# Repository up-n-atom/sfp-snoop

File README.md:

# sfp-snoop

SFP(+) cape for the [VCC-GND](https://vcc-gnd.com) [YD-RP2040](http://152.32.187.208:8080/yd-data/YD-RP2040/) pending a few modifications.

## Necessary YD-RP2040 Modifications

1. __Remove__ *D2, F1, U1, C1, C2*
2. __Bridge__ *D2* pins 1 and 2 with a 0Ohm 0603 resistor

__U1__ *(ME6215C33M5G)* and supporting components on the YD-RP2040 are replaced by __U1__ *(AIC1221-33GY3TR)* on the sfp-snoop 

## Pinout

| YD-RP2040 | [SFP (INF-8074i)](https://members.snia.org/document/dl/26184) | Transceivers |
| --        | --              | -- |
| 7 (GP5 - *USART1 RX*)   | 2 | Huawei SmartAX MA5671A, Alcatel-Lucent G-010S-P, BFW WAS-110 UART TX |
| 12 (GP8 - *USART1 TX*)  | 3 | Nokia G-010S-A UART RX |
| 9 (GP6 - *I2C1 SDA*)    | 4 | |
| 10 (GP7 - *I2C1 SCL*)   | 5 | |
| 11 (GP9 - *USART1 RX*)  | 6 | Nokia G-010S-A UART TX |
| 6 (GP4 - *USART1 TX*)   | 7 | Huawei SmartAX MA5671A, Alcatel-Lucent G-010S-P, BFW WAS-110 UART RX |
| 5 (GP3)                 | 8 | |
| 29 (GP22)               | 9 | |

* Short JP1
* Short R10 jumper to pin 37 (GP23) for user button power switch, or populate R10 with a 10KOhm 0603 resistor to access RGB LED (GP23)

## Bill of Materials

Total cost for single unit, incl. YD-RP2040 is around $5 USD.

| Ref.            | Value  | [LCSC](https://www.lcsc.com/) | Qty. |
| --              | --     | --                            | --:  |
| C1, C2          | 4.7uF  | [C1872](https://www.lcsc.com/product-detail/Multilayer-Ceramic-Capacitors-MLCC-SMD-SMT_Samsung-Electro-Mechanics-CL31B475KAHNNNE_C1872.html) | 2    |
| C3, C6, C9, C11 | 0.1uF  | [C282519](https://www.lcsc.com/product-detail/Multilayer-Ceramic-Capacitors-MLCC-SMD-SMT_CCTC-TCC0603X7R104K500CT_C282519.html) | 4    |
| C4              | 150uF   | [C542620](https://www.lcsc.com/product-detail/Tantalum-Capacitors_PANASONIC-6TPE150MAPB_C542620.html) | 1    |
| C7, C10         | 1uF    | [C59302](https://www.lcsc.com/product-detail/Multilayer-Ceramic-Capacitors-MLCC-SMD-SMT_FH-Guangdong-Fenghua-Advanced-Tech-0603B105K250NT_C59302.html) | 2    |
| C5, C8         | 0.01uF | [C525264](https://www.lcsc.com/product-detail/Multilayer-Ceramic-Capacitors-MLCC-SMD-SMT_PSA-Prosperity-Dielectrics-FN18X103K500PSG_C525264.html) | 2    |
| F1              | 2A     | [C261954](https://www.lcsc.com/product-detail/Resettable-Fuses_TLC-Electronic-TLC-NSMD100_C261954.html) | 1    |
| J1              | SFP+   | [C210158](https://www.lcsc.com/product-detail/Card-Edge-Connectors_TE-Connectivity-1367073-1_C210158.html) | 1    |
| J1 (Optional)   | SFP+ Cage   | [C7429382](https://www.lcsc.com/product-detail/Connector-Shells_HCTL-HC-SFP-03L_C7429382.html) | 1    |
| R1-R10           | 10KOhm | [C25804](https://www.lcsc.com/product-detail/Chip-Resistor-Surface-Mount_UNI-ROYAL-Uniroyal-Elec-0603WAF1002T5E_C25804.html) | 9 |
| U1              | AIC1221-33GY3TR | [C211622](https://www.lcsc.com/product-detail/Linear-Voltage-Regulators-LDO_AIC-Analog-Integrations-AIC1221-33GY3TR_C211622.html) | 1 |
| U2              | AP2191WG-7 | [C141321](https://www.lcsc.com/product-detail/Power-Distribution-Switches_Diodes-Incorporated-AP2191WG-7_C141321.html) | 1 |

| Ref.             | Value  | [AliExpress](https://www.aliexpress.com/) | Qty. |
| --               | --     | --                                        | --:  |
| J2, J3 *sfp-snoop* | Female | [2.54mm pitch, 20-pin Female Header](https://www.aliexpress.com/item/4000386969080.html) | 1 |

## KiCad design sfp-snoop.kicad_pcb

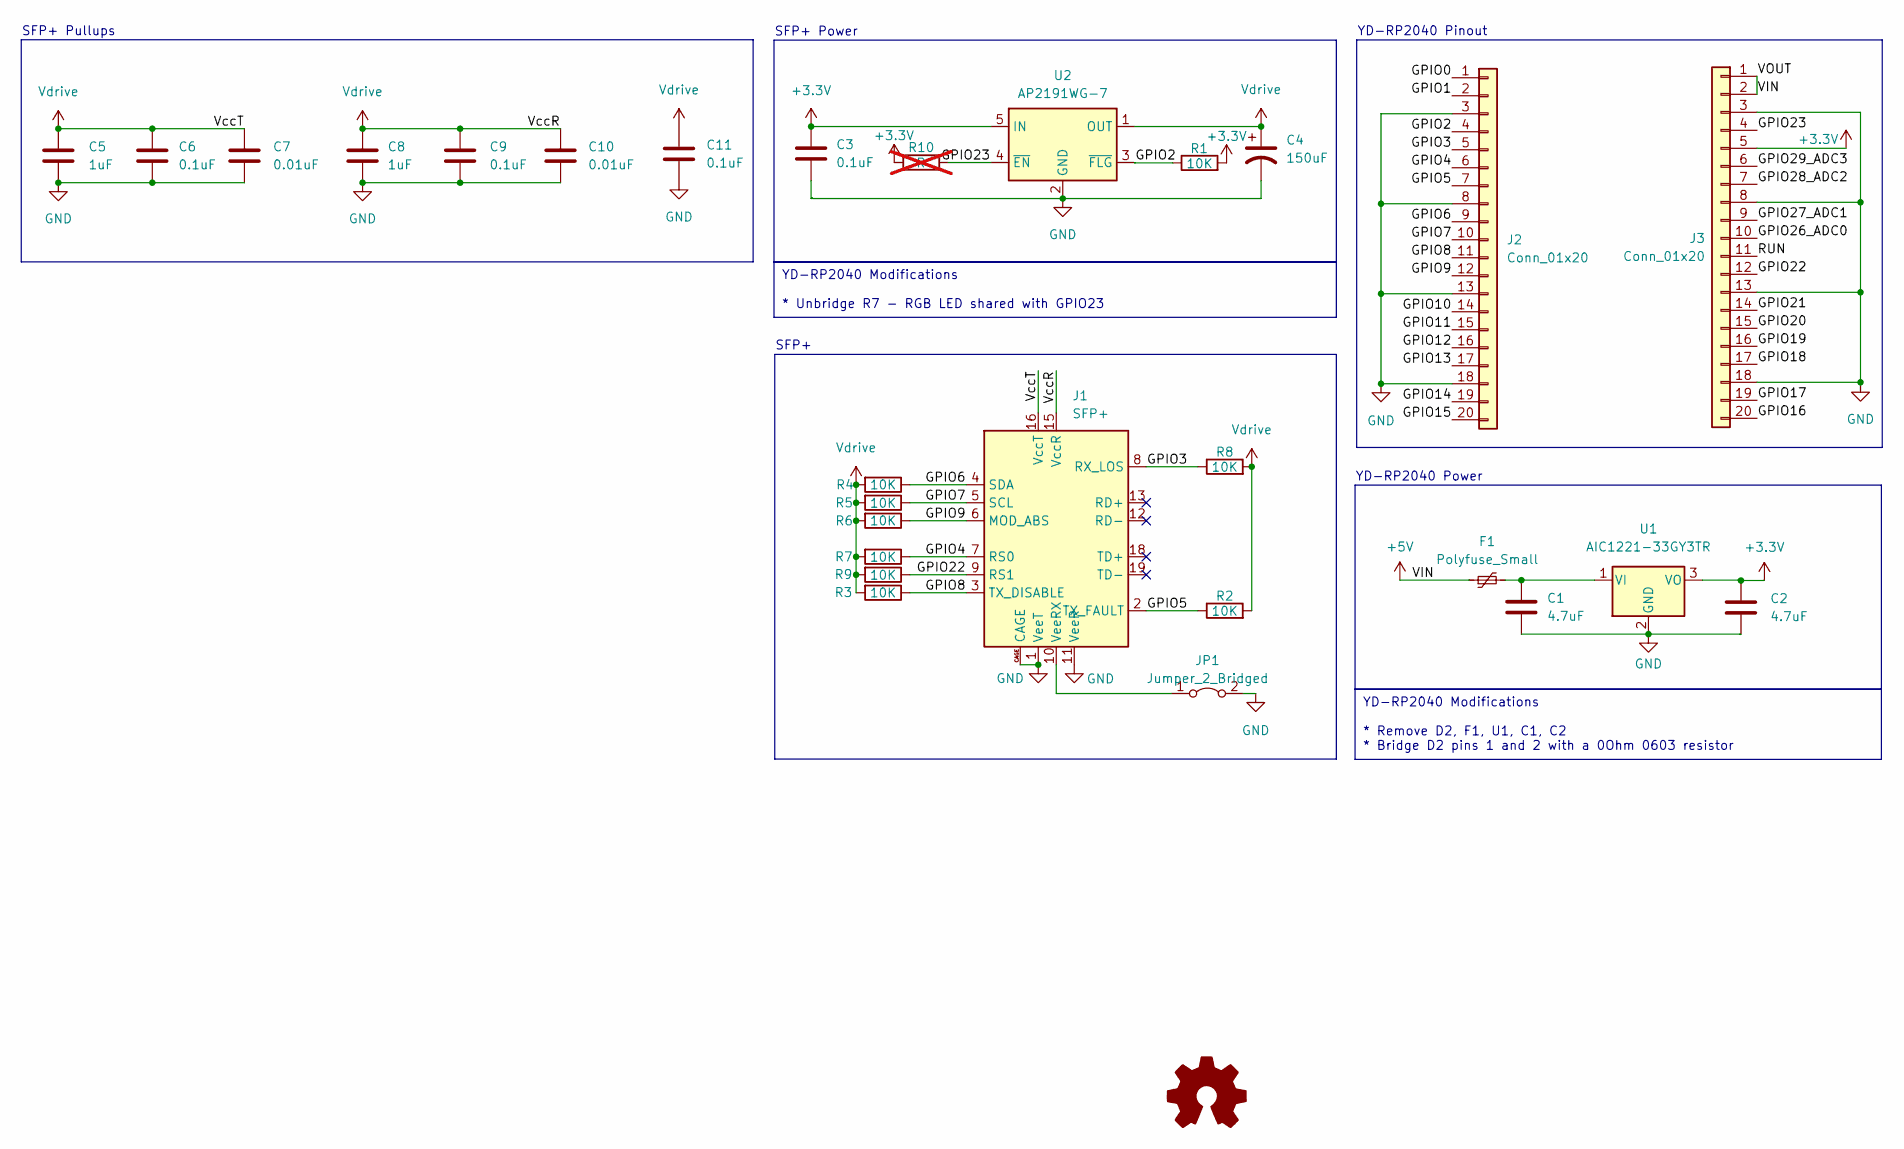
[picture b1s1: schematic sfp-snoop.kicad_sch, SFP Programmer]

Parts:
C1, C2: 4.7uF; C_1206_3216Metric; LCSC C1872
C3, C6, C9, C11: 0.1uF; C_0603_1608Metric; LCSC C282519
C4: 150uF; CP_EIA-3528-21_Kemet-B; LCSC C542620
C5, C8: 1uF; C_0603_1608Metric; LCSC C59302
C7, C10: 0.01uF; C_0603_1608Metric; LCSC C525264
F1: Polyfuse_Small; C_1206_3216Metric
J1: SFP+; Connector_SFP_and_Cage; LCSC C210158
J2, J3: Conn_01x20; PinSocket_1x20_P2.54mm_Vertical
JP1: Jumper_2_Bridged; SolderJumper-2_P1.3mm_Open_TrianglePad1.0x1.5mm
R1, R2, R3, R4, R5, R6, R7, R8, R9: 10K; R_0603_1608Metric; LCSC C25804
R10: R; R_0603_1608Metric; not fitted
U1: AIC1221-33GY3TR; SOT-223-3_TabPin2; LCSC C211622
U2: AP2191WG-7; SOT-23-5; LCSC C141321

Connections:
+3.3V: C2.1, C3.1, J3.5, R1.2, R10.1, U1.3 (VO), U2.5 (IN)
+5V: F1.1, J3.1, J3.2
/GPIO0: J2.1
/GPIO1: J2.2
/GPIO2: J2.4, R1.1, U2.3 (~FLG)
/GPIO3: J1.8 (RX_LOS), J2.5, R8.1
/GPIO4: J1.7 (RS0), J2.6, R7.1
/GPIO5: J1.2 (TX_FAULT), J2.7, R2.1
/GPIO6: J1.4 (SDA), J2.9, R4.1
/GPIO7: J1.5 (SCL), J2.10, R5.1
/GPIO8: J1.3 (TX_DISABLE), J2.11, R3.1
/GPIO9: J1.6 (MOD_ABS), J2.12, R6.1
/GPIO10: J2.14
/GPIO11: J2.15
/GPIO12: J2.16
/GPIO13: J2.17
/GPIO14: J2.19
/GPIO15: J2.20
/GPIO16: J3.20
/GPIO17: J3.19
/GPIO18: J3.17
/GPIO19: J3.16
/GPIO20: J3.15
/GPIO21: J3.14
/GPIO22: J1.9 (RS1), J3.12, R9.1
/GPIO23: J3.4, R10.2, U2.4 (~EN)
/GPIO26_ADC0: J3.10
/GPIO27_ADC1: J3.9
/GPIO28_ADC2: J3.7
/GPIO29_ADC3: J3.6
/RUN: J3.11
GND: C1.2, C2.2, C3.2, C4.2, C5.2, C6.2, C7.2, C8.2, C9.2, C10.2, C11.2, J1.1 (VeeT), J1.11 (VeeR), J1.14 (VeeR), J1.17 (VeeT), J1.20 (VeeT), J1.CAGE, J2.3, J2.8, J2.13, J2.18, J3.3, J3.8, J3.13, J3.18, JP1.2 (B), U1.2 (GND), U2.2 (GND)
unnamed: J1.10 (VeeRX), JP1.1 (A)
unnamed: C1.1, F1.2, U1.1 (VI)
Vdrive: C4.1, C5.1, C6.1, C7.1, C8.1, C9.1, C10.1, C11.1, J1.15 (VccR), J1.16 (VccT), R2.2, R3.2, R4.2, R5.2, R6.2, R7.2, R8.2, R9.2, U2.1 (OUT)

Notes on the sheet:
YD-RP2040 Modifications * Unbridge R7 - RGB LED shared with GPIO23
YD-RP2040 Modifications * Remove D2, F1, U1, C1, C2 * Bridge D2 pins 1 and 2 with a 0Ohm 0603 resistor
SFP+
SFP+ Pullups
SFP+ Power
YD-RP2040 Pinout
YD-RP2040 Power

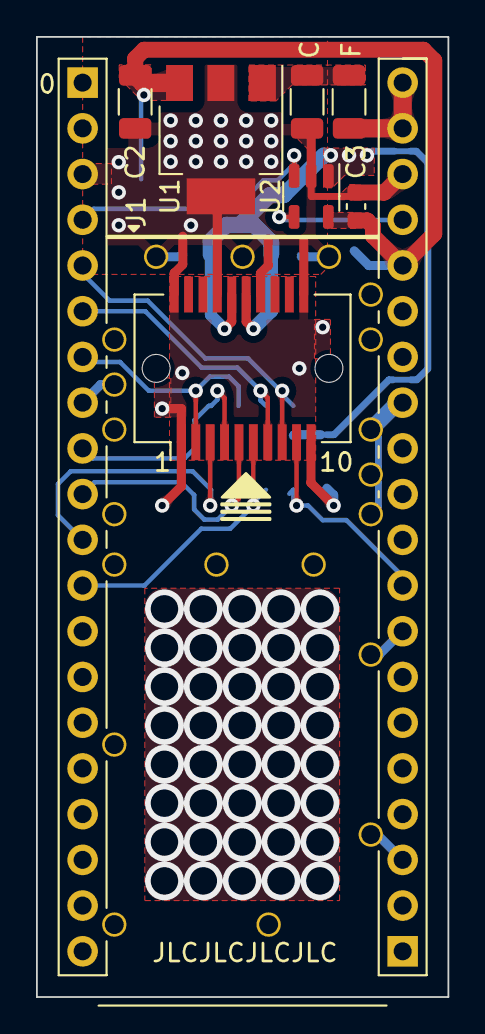
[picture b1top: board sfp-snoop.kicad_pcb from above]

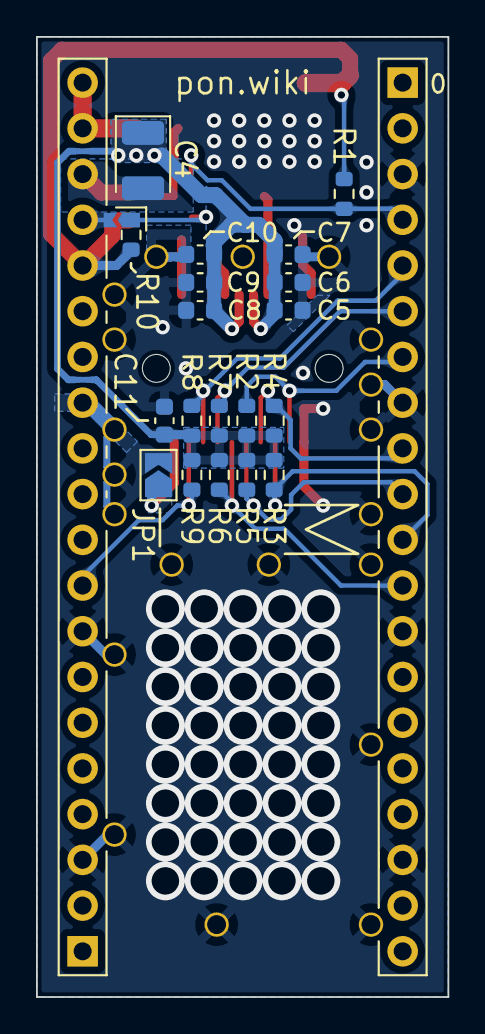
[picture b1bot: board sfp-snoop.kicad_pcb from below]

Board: 2 copper layers, 22.9 x 53.3 mm, 28 parts (19 on the bottom side), 16 nets.

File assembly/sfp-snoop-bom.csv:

"Reference","Value","Footprint","Datasheet","LCSC","Qty"
"C1, C2","4.7uF","Capacitor_SMD:C_1206_3216Metric","~","C1872","2"
"C3, C6, C9, C11","0.1uF","Capacitor_SMD:C_0603_1608Metric","~","C282519","4"
"C4","150uF","Capacitor_Tantalum_SMD:CP_EIA-3528-21_Kemet-B","~","C542620","1"
"C5, C8","1uF","Capacitor_SMD:C_0603_1608Metric","~","C59302","2"
"C7, C10","0.01uF","Capacitor_SMD:C_0603_1608Metric","~","C525264","2"
"F1","Polyfuse_Small","Capacitor_SMD:C_1206_3216Metric","~","","1"
"J1","SFP+","Connector:Connector_SFP_and_Cage","https://members.snia.org/document/dl/25892"," C210158","1"
"J2, J3","Conn_01x20","Connector_PinSocket_2.54mm:PinSocket_1x20_P2.54mm_Vertical","~","","2"
"JP1","Jumper_2_Bridged","Jumper:SolderJumper-2_P1.3mm_Open_TrianglePad1.0x1.5mm","~","","1"
"R1-R9","10K","Resistor_SMD:R_0603_1608Metric","~","C25804","9"
"R10","R","Resistor_SMD:R_0603_1608Metric","~","","1"
"U1","AIC1221-33GY3TR","Package_TO_SOT_SMD:SOT-223-3_TabPin2","https://www.analog.com.tw/ImgShow/DS-1221G-03.pdf","C211622","1"
"U2","AP2191WG-7","Package_TO_SOT_SMD:SOT-23-5","https://www.diodes.com/assets/Datasheets/AP2181_91.pdf","C141321","1"

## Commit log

2023-09-03 Add KiCad files
2023-09-03 Update README.md
    Add YD-RP2040 modifications
2023-09-03 Update README.md
    Add BOM
2023-09-03 Update README.md
    Add YD-RP2040 to INF-8074i pinout
2023-09-03 Update README.md
    Fix BOM C4 value
2023-09-04 GPIO23 jumper
2023-09-04 Generate gerbers
2023-09-04 Update README.md
    Document R10 jumper
2023-09-04 Update README.md
    Update PcbDraw back render
2023-09-04 Update README.md
    Add total cost
2023-09-04 Remove extra gerbers
2023-09-04 Update pcb
2023-10-08 Update Nokia G-010S-A pinout
2023-10-08 Update README.md
    Nokia G-010S-A pinout
2024-01-07 Update README.md
    Correct capacitor references and remove unnecessary elongated headers
